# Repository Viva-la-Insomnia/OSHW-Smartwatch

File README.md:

# OSHW-Smartwatch
This is a repo for EFM32-based smartwatch project.
-- Tuomas Tinus, Jimi Järvelin

Contribute by contacting us / sending in a pull request. 
Welcome additions: integration of https://github.com/NordicSemiconductor/ble-sdk-efm32/, USB code. 
Read the README in the Simplicity_project/ on Simplicity IDE setup details

Our code and hardware are GNU GPL v2 / CERN OHL v1.2, licenses are in the repo. 
However, note that external libraries used in this project are distributed under different licenses, e.g. ARM CMSIS is shared under BSD

Features of the project: 
 - EFM32 low-power microcontroller
 - Lithium battery-powered with charge over USB and battery gauging
 - Bluetooth Low-Energy interface
 - Inertial Measurement Unit (Accelerometer, Gyroscope, Magnetometer)
 - Sharp low-power memory display
 - Separate I2C EEPROM memory (up to 1MB in the current iteration)(switching to flash in the final version)
 - Possible password manager functionality with EFM32 hardware encryption

Current state of project: We have assembled a prototype and are debugging the software. Due to high workload the development has been promptly suspended and will resume in early June 2016

We would like to thank Jared Sanson - http://jared.geek.nz/2014/jul/oshw-oled-watch - for inspiration and design ideas.
Kris Winer - https://github.com/kriswiner/MPU-9250/ - for his MPU-9250 code

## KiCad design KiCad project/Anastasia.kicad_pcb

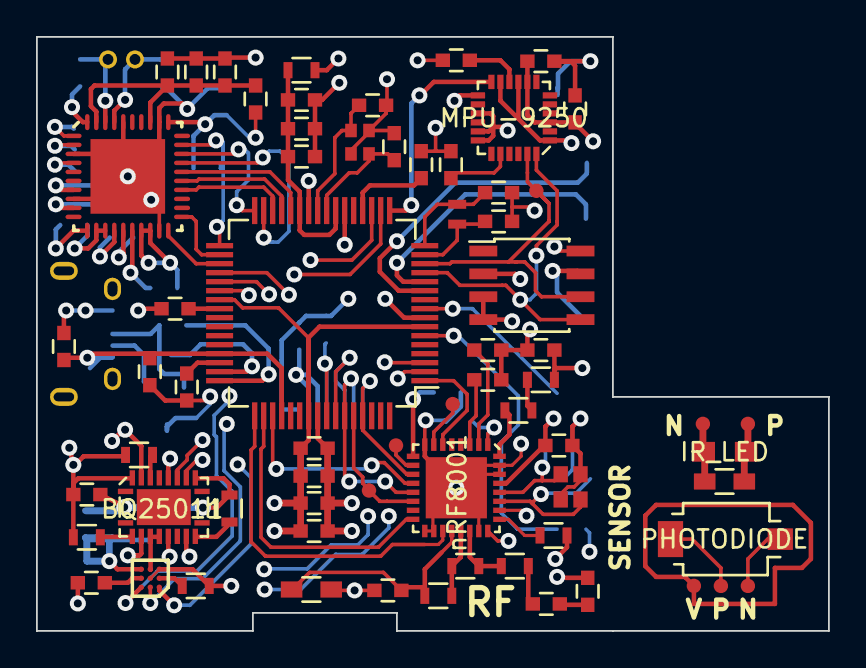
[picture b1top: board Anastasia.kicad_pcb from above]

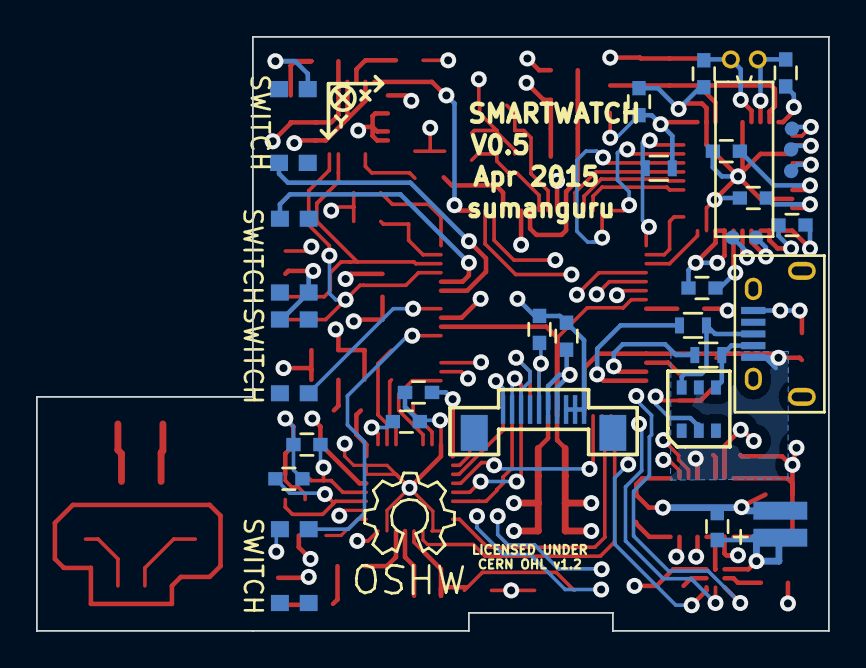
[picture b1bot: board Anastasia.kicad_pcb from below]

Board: 4 copper layers, 44.0 x 33.0 mm, 98 parts (31 on the bottom side), 83 nets.

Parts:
BT1: BATTERY
C1, C8, C9, C10, C13, C20, C23, C24, C30, C31, C32, C37, C41: 100N; C_0603
C2, C4, C26, C42: 1U; C_0603
C3, C14, C36: 4.7U; C_0603
C5, C11: 10U; C_0603
C6, C7, C21, C28, C29: 10N; C_0603
C12, C27, C33: 2.2U; C_0603
C15: 0.47U; C_0603
C16, C17: 15P; C_0603
C18, C19: 9P; C_0603
C22, C46: 2.2N; C_0603
C25: 2U; C_0603
C34, C35, C39, C40: 10P; C_0603
C38: 1N; C_0603
C43: 33N; C_0603
C44: 1.8N; C_0603
C45: 1.2N; C_0603
C47: N/C; R_0603_HandSoldering
CON1: USB-MICRO-B; USB_Micro-B
D1: PHOTODIODE; BPW34S
D2: RED_LED; R_0603_HandSoldering
D3: IR_LED; 2x1.25mm_LED
FB1: FB1; C_0603
L1: 47UH; R_0603
L2: 15NH; R_0603
L3: 10UH; R_0603
L4: 5.6NH; R_0603
L5: 8.2NH; R_0603
L6: 3.9NH; R_0603
P1: LS013B4DN04; FPC10
R1: 1R; R_0603
R2: 1K; R_0603
R3: 4K7; R_0603
R4, R6: 15R; R_0603
R5: 1.8M; R_0603
R7: 10K; R_0603
R8: 22K; R_0603
SW1, SW2, SW3, SW4: SWITCH; KMS_SMD_SW
TP7, TP11, TP17, TP18, TP19, TP20, TP21, TP22, TP23, TP24, TP25, TP26, TP27, TP28: TESTPAD; Test_Point_Round-SMD-Pad
U1: EFM32GG332; TQFP-64_10x10mm_Pitch0.5mm
U2: BQ25011; VQFN20
U3: BQ27421-G1; DSBGA9
U4: IP4220CZ6; SOT457
U5: MPU-9250; LGA24
U6: AT24C256; SOIC-8_3.9x4.9mm_Pitch1.27mm
U7: AFE4490; QFN40
U8: nRF8001; QFN32
X1: 32.768kHz SMD Crystal; 1.6x1.0CRYSTAL
X2: SMD_48MHZ_CRYSTAL_OSC; 2x1.6
X3: CRYSTAL; Crystal_Round_Horizontal_3mm
X4: CRYSTAL_SMD_16MHZ; 2x1.6CRYSTAL

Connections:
+3V3: C8.1, C9.1, C10.1, C11.1, C12.1, C20.1, C21.1, C25.1, C26.1, C31.1, C32.1, C36.1, C37.1, C38.1, C42.1, FB1.2, L1.1, L2.2, P1.6, P1.7, R1.2, R2.1, R7.1, U1.7, U1.26, U1.39, U1.55, U2.2, U5.3, U5.8, U5.13, U6.8, U7.11, U7.17, U7.18, U7.31, U8.1, U8.9, U8.24, U8.26, U8.29
/Bluetooth LE/ACTIVE: U1.1, U8.6
/Bluetooth LE/MISO: TP7.1, U1.60, U8.14
/Display/DISP_CLK: P1.1, U1.61, U8.11
/Display/DISP_CS: P1.3, U1.58
/Display/DISP_ON/OFF: C24.1, P1.5, U1.57
/Display/DISP_SI: P1.2, U1.59, U8.13
/IMU/IMU_INT: U1.17, U5.12
/Power/CE: U1.3, U2.15
/Power/GAUGE_SCL: U1.38, U3.A3
/Power/GAUGE_SDA: U1.37, U3.A2
/Power/GPOUT: U1.36, U3.A1
/Power/ISET: U1.2, U2.13
/Power/MCU_RESET: C1.1, U1.20
/Power/USB_DP: R4.1, U1.48
/Pulse oximeter /ADC_RDY: U1.32, U7.28
/Pulse oximeter /AFE_PDN: U1.35, U7.20
/Pulse oximeter /DIAG_END: U1.34, U7.21
/Pulse oximeter /MISO: U1.29, U7.25
/Pulse oximeter /MOSI: U1.28, U7.26
/Pulse oximeter /SCLK: U1.30, U7.24
/Pulse oximeter /SPIEN: U1.31, U7.27
/uC part A/PA9: U1.18, U2.7
/uC part A/PA10: U1.19, U2.8
/uC part B/I2C1_SCL: TP11.1, U1.14, U5.23, U6.6
/uC part B/I2C1_SDA: U1.13, U5.24, U6.5
/uC part B/PD5: R7.2, U1.33, U7.29
/uC part C/PF0: U1.49, U8.19
/uC part C/PF1: U1.50, U8.16
/uC part C/PF2: U1.51, U8.12
/uC part C/USB_DM: R6.1, U1.47
GND: BT1.2, C1.2, C2.2, C3.2, C4.2, C5.2, C6.2, C7.2, C8.2, C9.2, C10.2, C11.2, C12.2, C13.2, C14.2, C15.2, C16.1, C17.1, C18.1, C19.1, C20.2, C21.2, C22.2, C23.2, C24.2, C25.2, C26.2, C27.2, C28.2, C29.2, C30.2, C31.2, C32.2, C33.2, C34.2, C35.2, C36.2, C37.2, C38.2, C39.2, C40.2, C41.2, C42.2, C43.2, C45.2, C46.2, C47.2, CON1.5, CON1.6, CON1.7, CON1.8, CON1.9, P1.8, P1.9, P1.10, R3.1, R5.2, R8.1, SW1.2, SW2.4, SW3.4, SW4.4, U1.8, U1.22, U1.56, U2.3, U2.9, U2.18, U3.B2, U3.C1, U4.2, U5.1, U5.5, U5.9, U5.11, U5.15, U5.17, U5.18, U6.2, U6.3, U6.4, U6.7, U7.3, U7.8, U7.12, U7.13, U7.16, U7.19, U7.32, U7.36, U7.40, U7.41, U8.8, U8.17, U8.18, U8.23, U8.30, U8.31, U8.33, X2.3, X4.3
unnamed: BT1.1, C14.1, U3.C3
unnamed: C2.1, U1.40
unnamed: C4.1, U1.46
unnamed: C5.1, C6.1, C7.1, R1.1, U1.23, U1.27
unnamed: C15.1, U3.B3
unnamed: C16.2, U1.16, X1.1
unnamed: C17.2, U1.15, X1.2
unnamed: C18.2, U1.25, X2.1
unnamed: C19.2, U1.24, X2.2
unnamed: C22.1, U5.20
unnamed: C23.1, U5.10
unnamed: C27.1, U7.7
unnamed: C28.1, C29.1, C30.1, FB1.1, U7.33, U7.39
unnamed: C33.1, U7.9
unnamed: C34.1, U7.38, X3.1
unnamed: C35.1, U7.37, X3.2
unnamed: C39.1, U8.27, X4.1
unnamed: C40.1, U8.28, X4.2
unnamed: C41.1, U8.2
unnamed: C43.1, U8.3
unnamed: C44.1, L6.1
unnamed: C44.2, C45.1
unnamed: C46.1, C47.1, L4.1, U8.20
unnamed: CON1.2, R6.2, U4.4
unnamed: CON1.3, R4.2, U4.6
unnamed: D1.1, TP19.1
unnamed: D1.2, TP22.1
unnamed: D2.1, D3.2, TP25.1
unnamed: D2.2, D3.1, TP27.1
unnamed: L1.2, U2.19
unnamed: L2.1, L3.2
unnamed: L3.1, U8.32
unnamed: L4.2, L5.1, U8.21
unnamed: L5.2, L6.2, U8.22
unnamed: R2.2, U2.4
unnamed: R3.2, U2.12
unnamed: R5.1, U3.B1
unnamed: R8.2, U8.25
unnamed: SW1.3, U1.11
unnamed: SW2.1, U1.12
unnamed: SW3.1, U1.9
unnamed: SW4.3, U1.6
unnamed: TP17.1, U8.7
unnamed: TP18.1, U8.10
unnamed: TP20.1, U7.4
unnamed: TP21.1, U7.1
unnamed: TP24.1, U7.2
unnamed: TP26.1, U7.14
unnamed: TP28.1, U7.15
unnamed: U2.16, U2.17, U3.C2
USB_VBUS: C3.1, C13.1, CON1.1, U1.45, U1.52, U2.6, U4.5

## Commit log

2015-03-14 Create TODO
2015-03-14 Create BOM&Features
2015-03-14 KiCad project file import
    Schematics & libraries for the project
2015-03-14 Power and USB schematics
2015-03-14 Power and USB schematics
    The actual schematics file updates
2015-03-15 IMU and crystal schematics
    Added schematics for crystal oscillators of the main uC and schematic
    for MPU-9150 and passive components. Miscellaneous updates and
    annotations
2015-03-16 Bluetooth schematics
    nRF8001 schematics, various additions and modification, test points
    added
2015-03-16 BOM additions
2015-03-17 Create Power Consumption (no LEDs)
2015-03-18 Update Power Consumption
2015-03-21 EEPROM schematics
2015-03-21 IC packages, bugfixes
    drawings for IC packages, associations, schematic fixes
2015-03-21 New packages, PCB
2015-03-23 Schematics, PCB design
    New schematics for the pulse oximeter, PCB layout design
2015-03-26 PCB design
    Routing for the main components, except for the power section
2015-04-07 PCB finalised, Gerbers created for v0.5
    New footprints, fixes in schematic, PCB final design, plotted Gerbers
    for prototype production
2015-05-05 Refactoring and documentation
2015-05-05 Refactoring
2015-05-05 Refactoring and assembly assist files
2015-05-24 Rename LICENSE to SW_LICENSE
2015-05-28 Create HW_LICENSE
2015-05-28 Modifications for compliance with CERN OHL
2015-05-30 Software setup
2015-06-16 Interface code for BQ25010
2015-06-19 Initial code for BQ27421 interfacing
2015-06-22 First version of MPU-9250 code
2015-06-23 Small bugfixes and AFE4490 lib template
2015-09-17 Solder stencil files and misc. corrections
2015-09-24 Misc.
2015-10-02 Refactoring, mods for easier accessibility, cleanup, port to IDE v3.1
2015-10-09 Memory display interfacing, delay routines, misc
2015-12-02 Major alterations to display drivers and refactoring
2015-12-02 Moving graphics to a dedicated library
2015-12-03 Major interface library additions, refactoring
2015-12-03 Readme changes
2015-12-17 Preliminary changes to display drivers
2015-12-17 Create Design TODO
2015-12-19 Fixes to display drivers
2015-12-19 Sprite rendering mechanics, new demo code

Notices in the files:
KiCad project/Anastasia.kicad_pcb:
LICENSED UNDER
CERN OHL v1.2
